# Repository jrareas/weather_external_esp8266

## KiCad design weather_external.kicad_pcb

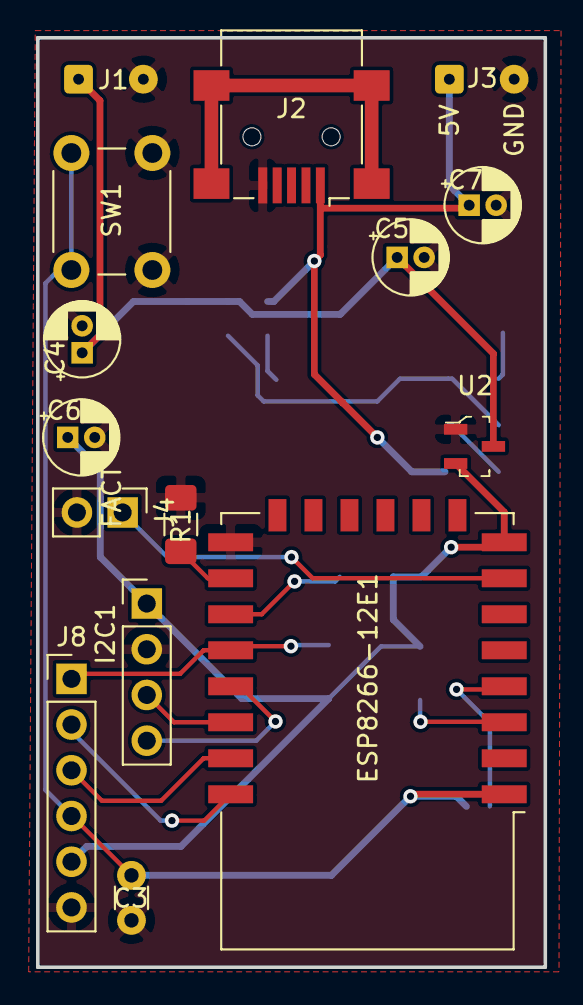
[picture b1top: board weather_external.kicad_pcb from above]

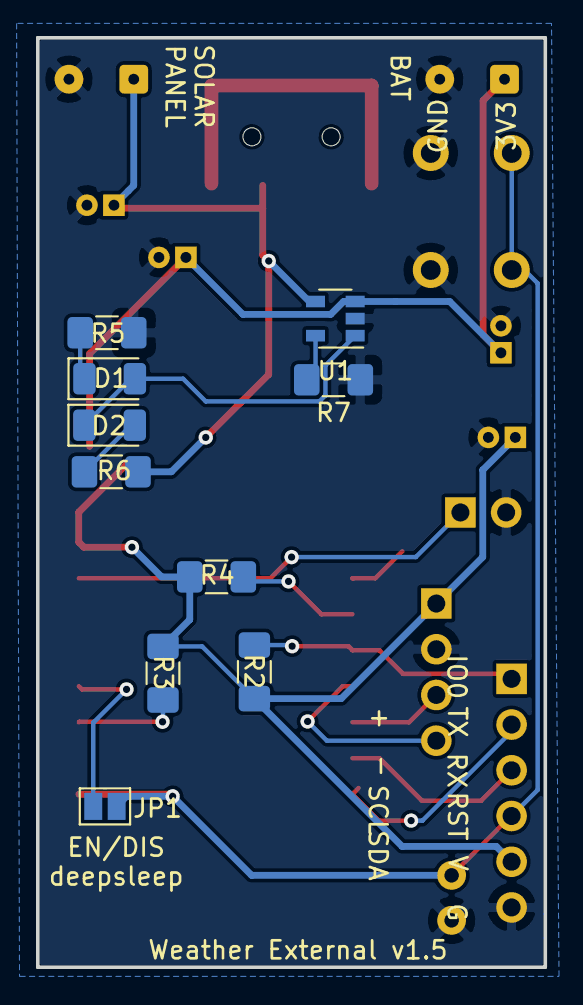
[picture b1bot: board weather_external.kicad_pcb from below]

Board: 2 copper layers, 28.2 x 51.6 mm, 25 parts (10 on the bottom side), 19 nets.

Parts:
C3: 100nf; C_Disc_D3.0mm_W1.6mm_P2.50mm
C4, C7: CP; CP_Radial_D4.0mm_P1.50mm
C5, C6: 10nF; CP_Radial_D4.0mm_P1.50mm
D1: GREEN; LED_1206_3216Metric
D2: RED; LED_1206_3216Metric
ESP8266-12E1: ESP8266-12E_ESP-12E; ESP-12E
I2C1: Conn_01x04_Male; PinHeader_1x04_P2.54mm_Vertical
J1: Battery; SolderWire-0.1sqmm_1x02_P3.6mm_D0.4mm_OD1mm
J2: USB_B_Mini; USB_Mini-B_Lumberg_2486_01_Horizontal
J3: Solar Panel; SolderWire-0.1sqmm_1x02_P3.6mm_D0.4mm_OD1mm
J4: Conn_01x02_Male; PinHeader_1x02_P2.54mm_Vertical
J8: FTDI; PinHeader_1x06_P2.54mm_Vertical
JP1: Jumper_NO_Small; SolderJumper-2_P1.3mm_Open_Pad1.0x1.5mm
R1: 10k; R_1206_3216Metric_Pad1.42x1.75mm_HandSolder
R2, R3, R4: 12k; R_1206_3216Metric_Pad1.42x1.75mm_HandSolder
R5, R6: 220; R_1206_3216Metric_Pad1.42x1.75mm_HandSolder
R7: 2k; R_1206_3216Metric_Pad1.42x1.75mm_HandSolder
SW1: SW_Push; SW_PUSH_6mm_H4.3mm
U1: MCP73831-2-OT; SOT-23-5
U2: MCP1700T-3302E_TT; SOT-23-3

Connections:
+3V3: C6.1, ESP8266-12E1.8, I2C1.1, J8.5, R2.1, R3.1, R4.1, U2.2
EN: ESP8266-12E1.3, R3.2
GND: C3.1, C4.2, C5.2, C6.2, C7.2, ESP8266-12E1.15, I2C1.2, J1.2, J2.5, J3.2, J4.2, J8.6, R1.1, R5.2, R7.1, SW1.1, U1.2, U2.1
GPIO0: ESP8266-12E1.18, J8.1, R2.2
GPIO2: ESP8266-12E1.17, R4.2
GPIO13: ESP8266-12E1.7, J4.1
GPIO15: ESP8266-12E1.16, R1.2
GPIO16: ESP8266-12E1.4, JP1.1
unnamed: D1.1, R5.1
unnamed: D1.2, D2.1, U1.1
unnamed: D2.2, R6.1
unnamed: R7.2, U1.5
RST: C3.2, ESP8266-12E1.1, J8.4, JP1.2, SW1.2
RX: ESP8266-12E1.21, J8.3
SCL: ESP8266-12E1.20, I2C1.3
SDA: ESP8266-12E1.19, I2C1.4
TX: ESP8266-12E1.22, J8.2
VBAT: C4.1, C5.1, J1.1, U1.3, U2.3
VCC: C7.1, J2.1, J3.1, R6.2, U1.4

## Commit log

2020-10-14 First commit. JLCPCB version 1
2020-10-20 Version 1.2. Small components
2020-10-20 Version with 555
2020-10-21 SMD Components
2020-10-27 no 555 Print version
2020-10-28 JLCPCB version 1.3
2020-10-29 No 555 jlcpcb 1206 resistors
2020-11-16 - Adding charger module TP4056 - add usb
2020-11-16 Fixing some labels
2020-11-18 - Using MCP73831 to manage battery charging
2020-11-25 V1.4 - adding jumper to reset configurations(wifi and custom)
2020-11-26 V1.4 - changing version in the sheet
2020-11-28 Fixing FTDI labels
2020-11-29 - Moving BME280 farther from the ESP8266 Antenna - keeping the version
2020-11-29 - removing some sharp corners
2020-12-04 V1.5 removing battery charger components
2020-12-17 V 1.5 - no load management once it is built to run in solar panel charging mode
